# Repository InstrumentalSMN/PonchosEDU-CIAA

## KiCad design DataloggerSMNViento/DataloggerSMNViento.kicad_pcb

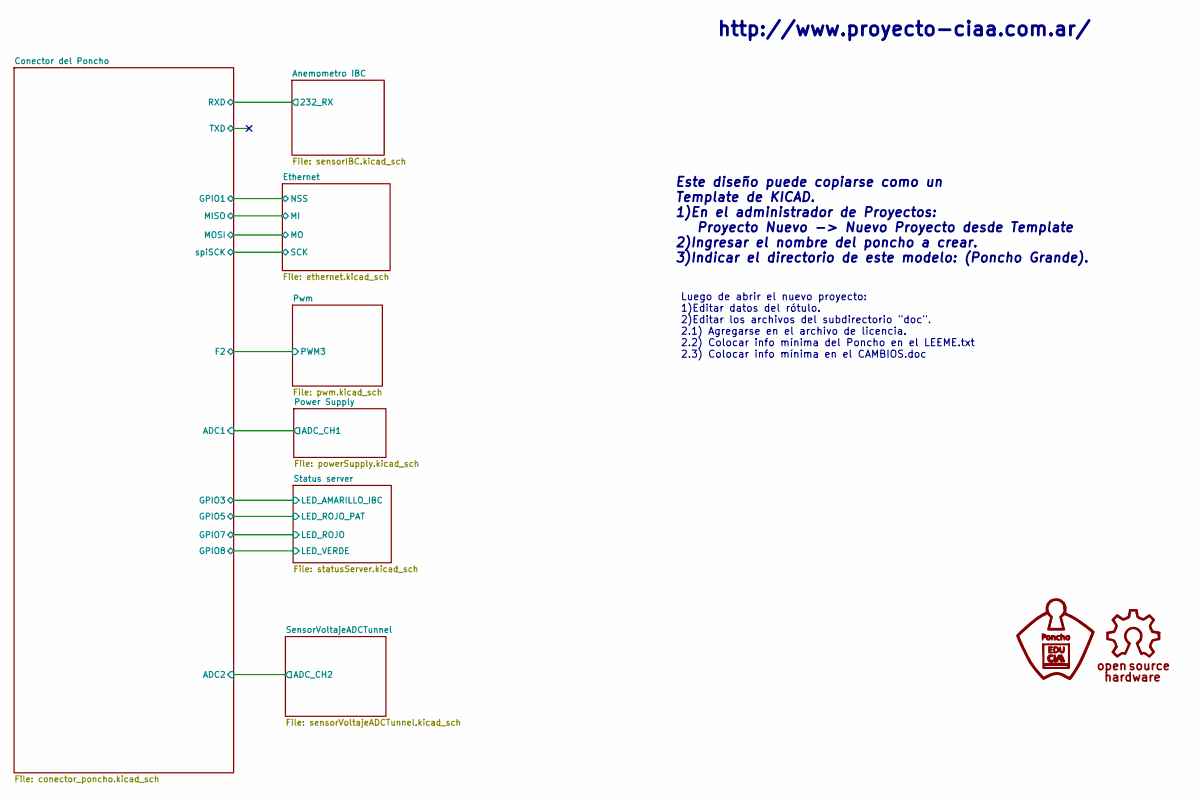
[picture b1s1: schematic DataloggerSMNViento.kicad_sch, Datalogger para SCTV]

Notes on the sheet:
Este diseño puede copiarse como un Template de KICAD. 1)En el administrador de Proyectos: Proyecto Nuevo -> Nuevo Proyecto desde Template 2)Ingresar el nombre del poncho a crear. 3)Indicar el directorio de este modelo: (Poncho Grande).
http://www.proyecto-ciaa.com.ar/
Luego de abrir el nuevo proyecto: 1)Editar datos del rótulo. 2)Editar los archivos del subdirectorio "doc". 2.1) Agregarse en el archivo de licencia. 2.2) Colocar info mínima del Poncho en el LEEME.txt 2.3) Colocar info mínima en el CAMBIOS.doc

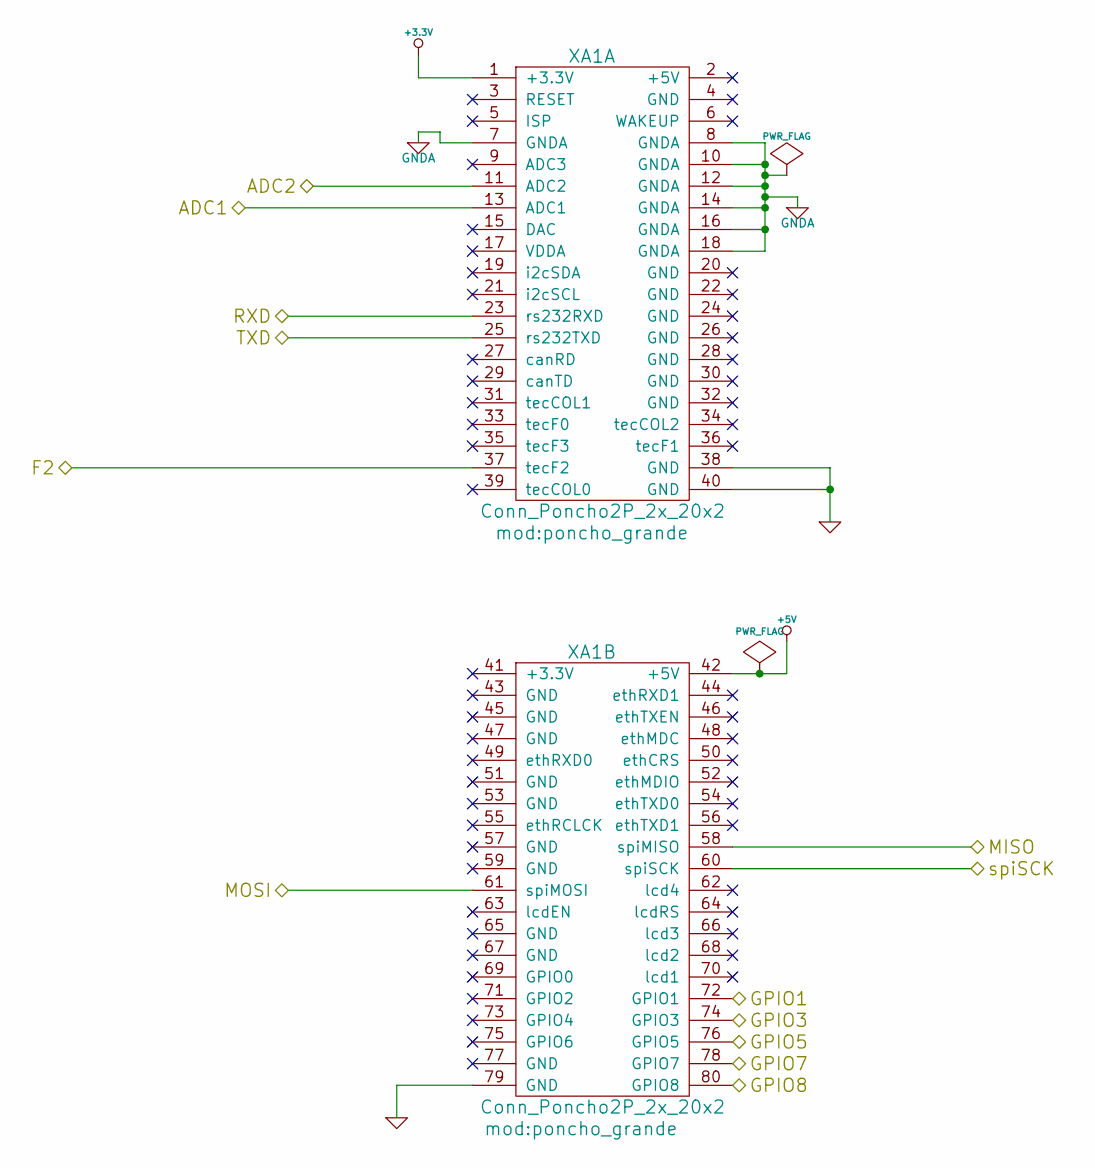
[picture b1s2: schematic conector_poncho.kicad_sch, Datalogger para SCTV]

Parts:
XA1: Conn_Poncho2P_2x_20x2; poncho_grande

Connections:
+3.3V: XA1.1 (+3.3V); also elsewhere on the board
+5V: XA1.42 (+5V); also elsewhere on the board
/Anemometro IBC/232_RX: XA1.23 (rs232RXD); also elsewhere on the board
/Conector del Poncho/ADC1: XA1.13 (ADC1); also elsewhere on the board
/Conector del Poncho/ADC2: XA1.11 (ADC2); also elsewhere on the board
/Conector del Poncho/F2: XA1.37 (tecF2); also elsewhere on the board
/Conector del Poncho/GPIO1: XA1.72 (GPIO1); also elsewhere on the board
/Conector del Poncho/GPIO3: XA1.74 (GPIO3); also elsewhere on the board
/Conector del Poncho/GPIO5: XA1.76 (GPIO5); also elsewhere on the board
/Conector del Poncho/GPIO7: XA1.78 (GPIO7); also elsewhere on the board
/Conector del Poncho/GPIO8: XA1.80 (GPIO8); also elsewhere on the board
/Conector del Poncho/MISO: XA1.58 (spiMISO); also elsewhere on the board
/Conector del Poncho/MOSI: XA1.61 (spiMOSI); also elsewhere on the board
/Conector del Poncho/TXD: XA1.25 (rs232TXD)
/Conector del Poncho/spiSCK: XA1.60 (spiSCK); also elsewhere on the board
GNDA: XA1.7 (GNDA), XA1.8 (GNDA), XA1.10 (GNDA), XA1.12 (GNDA), XA1.14 (GNDA), XA1.16 (GNDA), XA1.18 (GNDA); also elsewhere on the board
GNDinVariador: XA1.38 (GND), XA1.40 (GND), XA1.79 (GND); also elsewhere on the board

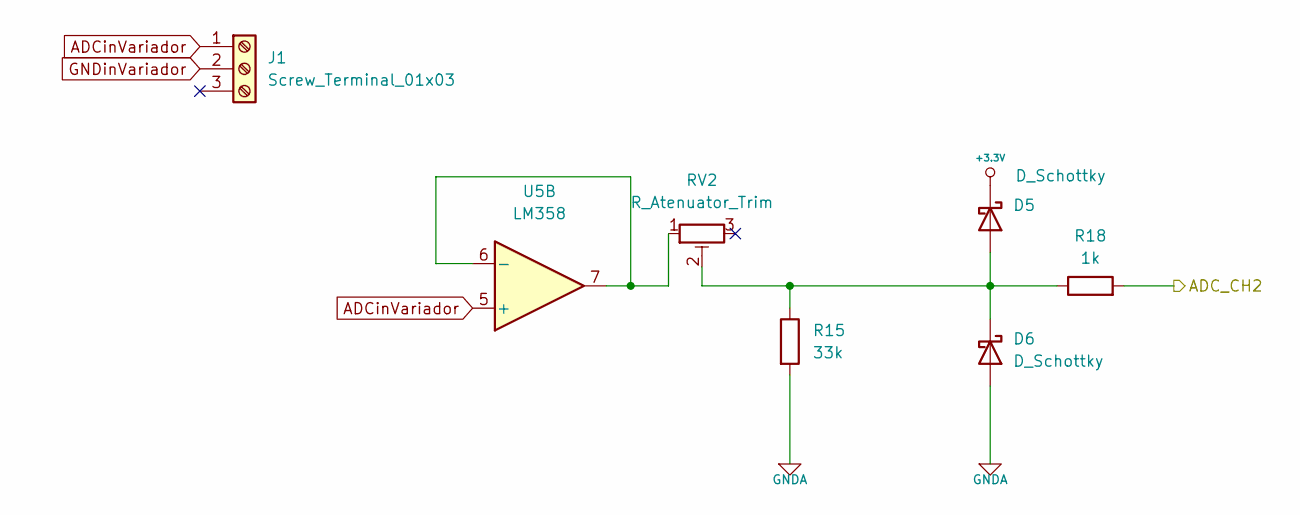
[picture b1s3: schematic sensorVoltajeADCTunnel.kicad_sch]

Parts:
D5, D6: D_Schottky; D_SOD-128
J1: Screw_Terminal_01x03; TerminalBlock_Altech_AK300-3_P5.00mm
R15: 33k; R_1206_3216Metric
R18: 1k; R_1206_3216Metric
RV2: R_Atenuator_Trim; PinHeader_1x03_P2.54mm_Vertical
U5: LM358; SOIC-8_3.9x4.9mm_P1.27mm

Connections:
+3.3V: D5.1 (K); also elsewhere on the board
/Conector del Poncho/ADC2: R18.2; also elsewhere on the board
ADCinVariador: J1.1, U5.5 (+); also elsewhere on the board
GNDA: D6.2 (A), R15.2; also elsewhere on the board
GNDinVariador: J1.2; also elsewhere on the board
unnamed: D5.2 (A), D6.1 (K), R15.1, R18.1, RV2.2
unnamed: RV2.1, U5.6 (-), U5.7

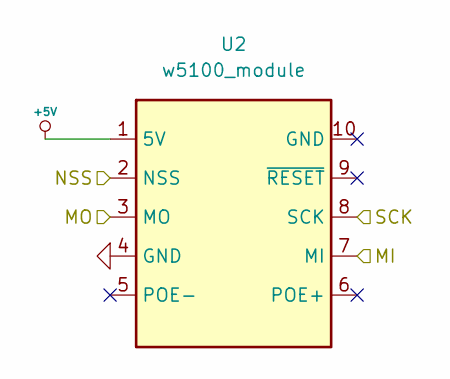
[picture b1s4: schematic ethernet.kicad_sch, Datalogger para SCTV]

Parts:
U2: w5100_module; W5100_module

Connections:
+5V: U2.1 (5V); also elsewhere on the board
/Conector del Poncho/GPIO1: U2.2 (NSS); also elsewhere on the board
/Conector del Poncho/MISO: U2.7 (MI); also elsewhere on the board
/Conector del Poncho/MOSI: U2.3 (MO); also elsewhere on the board
/Conector del Poncho/spiSCK: U2.8 (SCK); also elsewhere on the board
GNDinVariador: U2.4 (GND); also elsewhere on the board

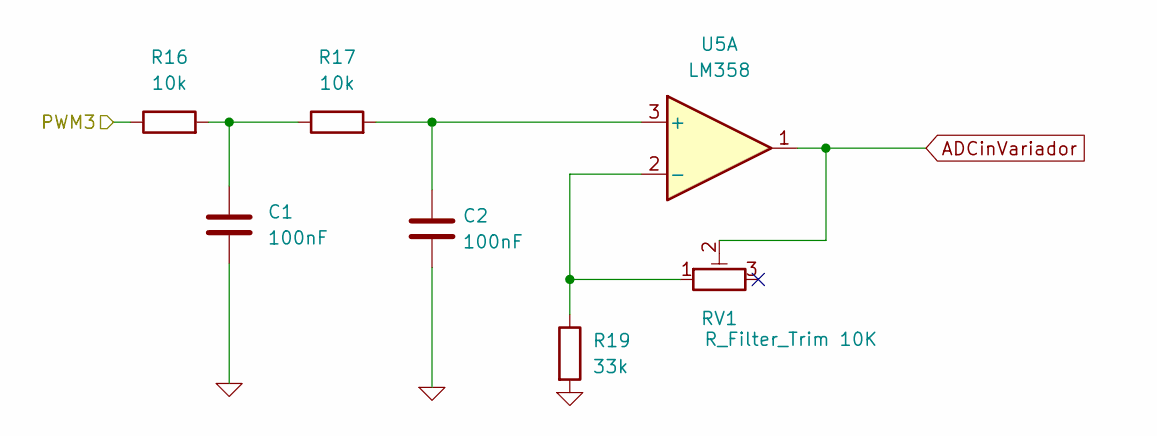
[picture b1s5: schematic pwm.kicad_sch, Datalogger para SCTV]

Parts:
C1, C2: 100nF; C_1206_3216Metric
R16, R17: 10k; R_1206_3216Metric
R19: 33k; R_1206_3216Metric
RV1: R_Filter_Trim 10K; PinHeader_1x03_P2.54mm_Vertical
U5: LM358; SOIC-8_3.9x4.9mm_P1.27mm

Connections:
/Conector del Poncho/F2: R16.1; also elsewhere on the board
ADCinVariador: RV1.2, U5.1; also elsewhere on the board
GNDinVariador: C1.2, C2.2, R19.2; also elsewhere on the board
unnamed: C1.1, R16.2, R17.1
unnamed: C2.1, R17.2, U5.3 (+)
unnamed: R19.1, RV1.1, U5.2 (-)

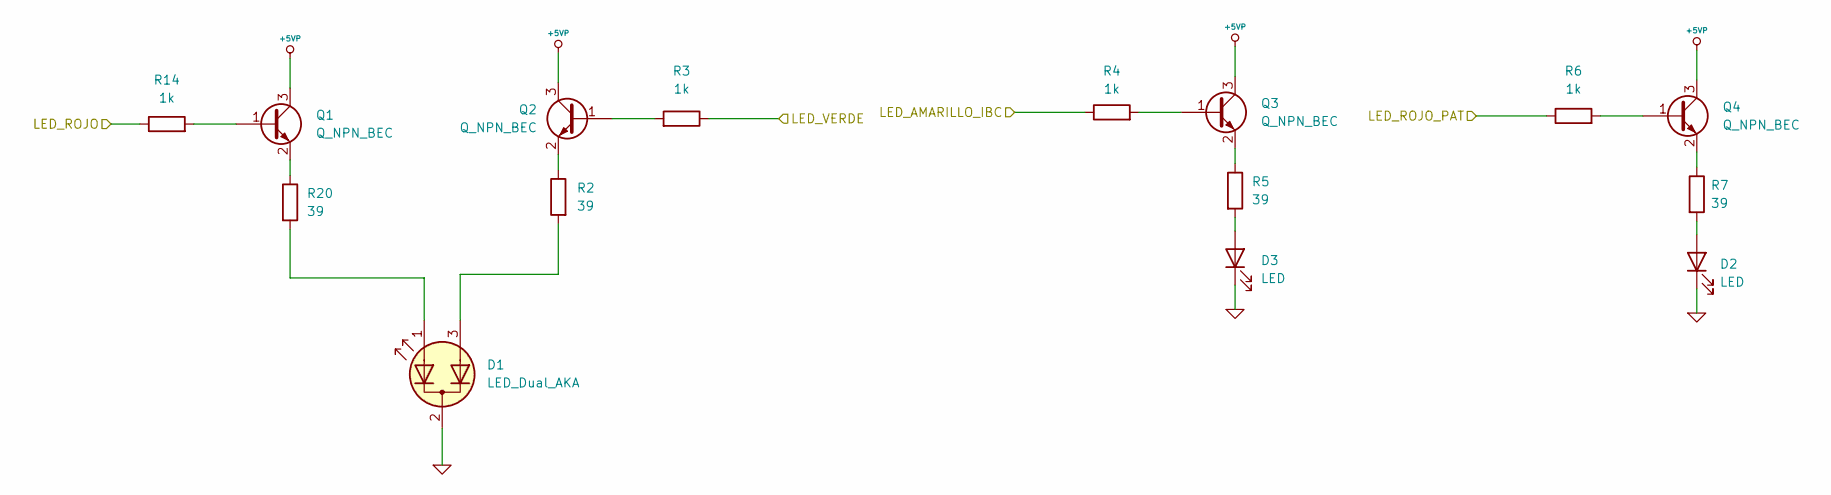
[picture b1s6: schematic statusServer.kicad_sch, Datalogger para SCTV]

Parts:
D1: LED_Dual_AKA; LED_D3.0mm-3
D2, D3: LED; LED_D3.0mm
Q1, Q2, Q3, Q4: Q_NPN_BEC; SOT-23
R2, R5, R7, R20: 39; R_1206_3216Metric
R3, R4, R6, R14: 1k; R_1206_3216Metric

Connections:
+5VP: Q1.3 (C), Q2.3 (C), Q3.3 (C), Q4.3 (C); also elsewhere on the board
/Conector del Poncho/GPIO3: R4.1; also elsewhere on the board
/Conector del Poncho/GPIO5: R6.1; also elsewhere on the board
/Conector del Poncho/GPIO7: R14.1; also elsewhere on the board
/Conector del Poncho/GPIO8: R3.1; also elsewhere on the board
GNDinVariador: D1.2 (K), D2.1 (K), D3.1 (K); also elsewhere on the board
unnamed: D1.1 (A1), R20.2
unnamed: D1.3 (A2), R2.2
unnamed: D2.2 (A), R7.2
unnamed: D3.2 (A), R5.2
unnamed: Q1.1 (B), R14.2
unnamed: Q1.2 (E), R20.1
unnamed: Q2.1 (B), R3.2
unnamed: Q2.2 (E), R2.1
unnamed: Q3.1 (B), R4.2
unnamed: Q3.2 (E), R5.1
unnamed: Q4.1 (B), R6.2
unnamed: Q4.2 (E), R7.1

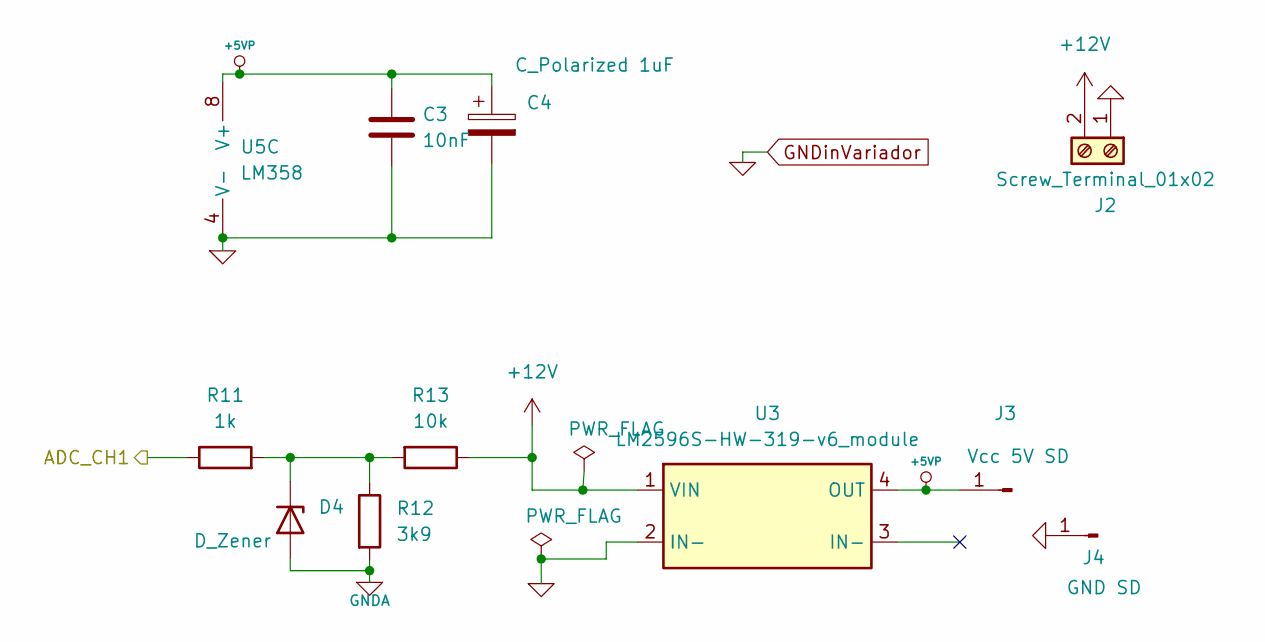
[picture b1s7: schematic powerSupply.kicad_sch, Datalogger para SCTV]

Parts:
C3: 10nF; C_1206_3216Metric
C4: C_Polarized 1uF; CP_Elec_4x5.3
D4: D_Zener; D_DO-34_SOD68_P7.62mm_Horizontal
J2: Screw_Terminal_01x02; TerminalBlock_Altech_AK300-2_P5.00mm
J3: Vcc 5V SD; PinHeader_1x01_P2.54mm_Vertical
J4: GND SD; PinHeader_1x01_P2.54mm_Vertical
R11: 1k; R_1206_3216Metric
R12: 3k9; R_1206_3216Metric
R13: 10k; R_1206_3216Metric
U3: LM2596S-HW-319-v6_module; LM2596_StepDown
U5: LM358; SOIC-8_3.9x4.9mm_P1.27mm

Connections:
+5VP: C3.1, C4.1, J3.1, U3.4 (OUT), U5.8 (V+); also elsewhere on the board
+12V: J2.2, R13.1, U3.1 (VIN)
/Conector del Poncho/ADC1: R11.1; also elsewhere on the board
GNDA: D4.2 (A), R12.2; also elsewhere on the board
GNDinVariador: C3.2, C4.2, J2.1, J4.1, U3.2 (IN-), U5.4 (V-); also elsewhere on the board
unnamed: D4.1 (K), R11.2, R12.1, R13.2

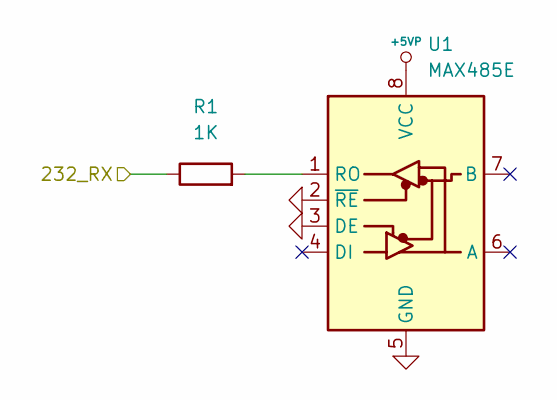
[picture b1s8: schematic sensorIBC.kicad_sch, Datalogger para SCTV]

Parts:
R1: 1K; R_1206_3216Metric
U1: MAX485E; Rs485toTTL

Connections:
+5VP: U1.8 (VCC); also elsewhere on the board
/Anemometro IBC/232_RX: R1.1; also elsewhere on the board
GNDinVariador: U1.2 (~RE), U1.3 (DE), U1.5 (GND); also elsewhere on the board
unnamed: R1.2, U1.1 (RO)

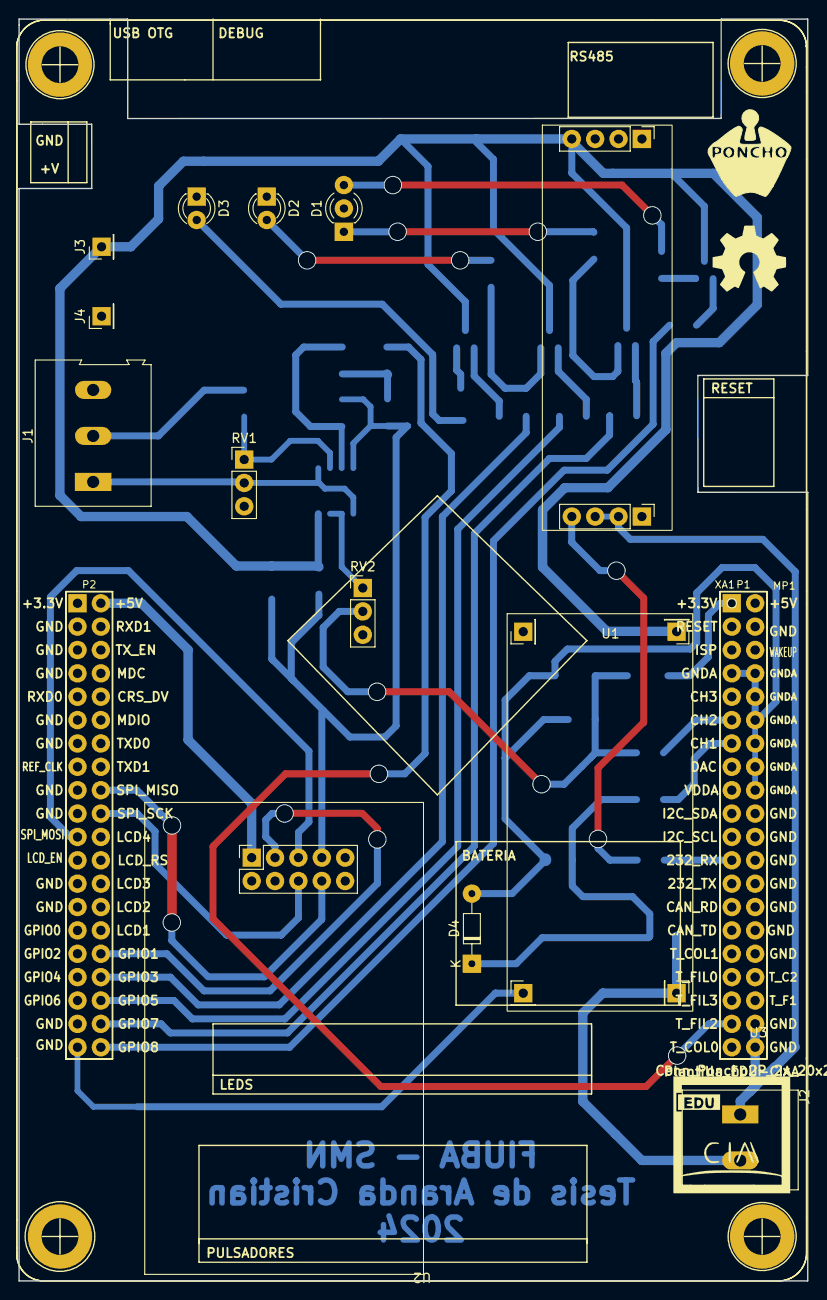
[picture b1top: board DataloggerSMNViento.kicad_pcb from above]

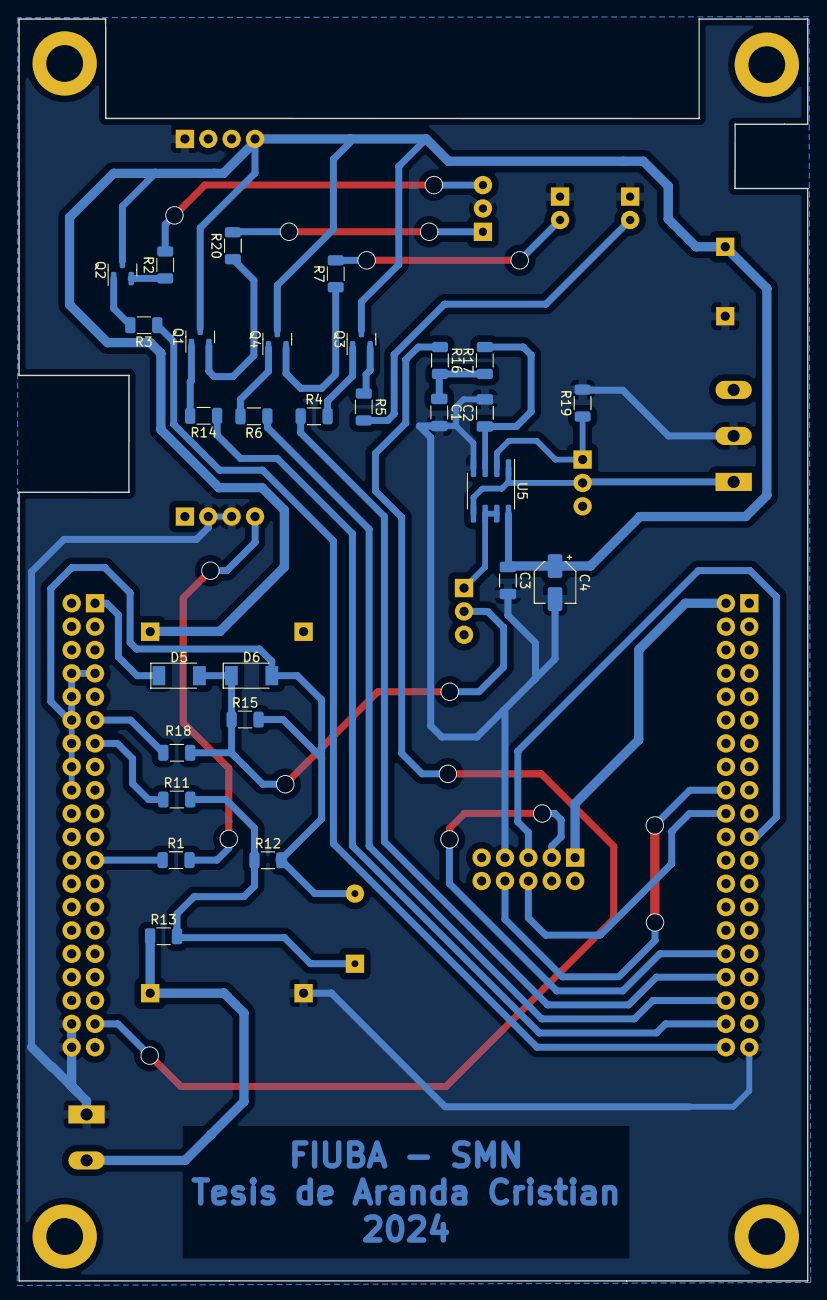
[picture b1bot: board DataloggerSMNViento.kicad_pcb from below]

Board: 2 copper layers, 85.7 x 137.2 mm, 44 parts (28 on the bottom side), 38 nets.

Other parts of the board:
G101: Logo_OSHWA
MP1: Plantilla_EDU-CIAA

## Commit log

2023-10-12 Se agrego un shield (Poncho) para el datalogger del tunel de viento
2023-10-20 Agrego el esquemático del poncho Datalogger para SCTV
2024-03-25 Agrego modificaciones al poncho de la EDU CIAA, también agrego una simulacion del circuito para tomar la tensión del ADC del tunnel
2024-04-22 Subo la version v1.0 del PCB del poncho de la tesis
2024-04-24 Se cambio la alimentacion de los modulos por el stepDown
2024-04-25 Se cambio el diodo zener de SMD a THT
2024-04-25 Se va agregar una rama develop y dos ramas PCB THT y PCB SMD dél proyecto dataloggerSMN
2024-04-25 Se va a agregar las ramas para el desarrollo en doble y simple faz
2024-04-25 Subo la version v1.2 THT de la poncho, para fabricar en el SMN
2024-05-08 Se debe cambiar el diseño porque el footprint del StepDown esta invertido, lo cual va a implicar cambiar algunas pistas
